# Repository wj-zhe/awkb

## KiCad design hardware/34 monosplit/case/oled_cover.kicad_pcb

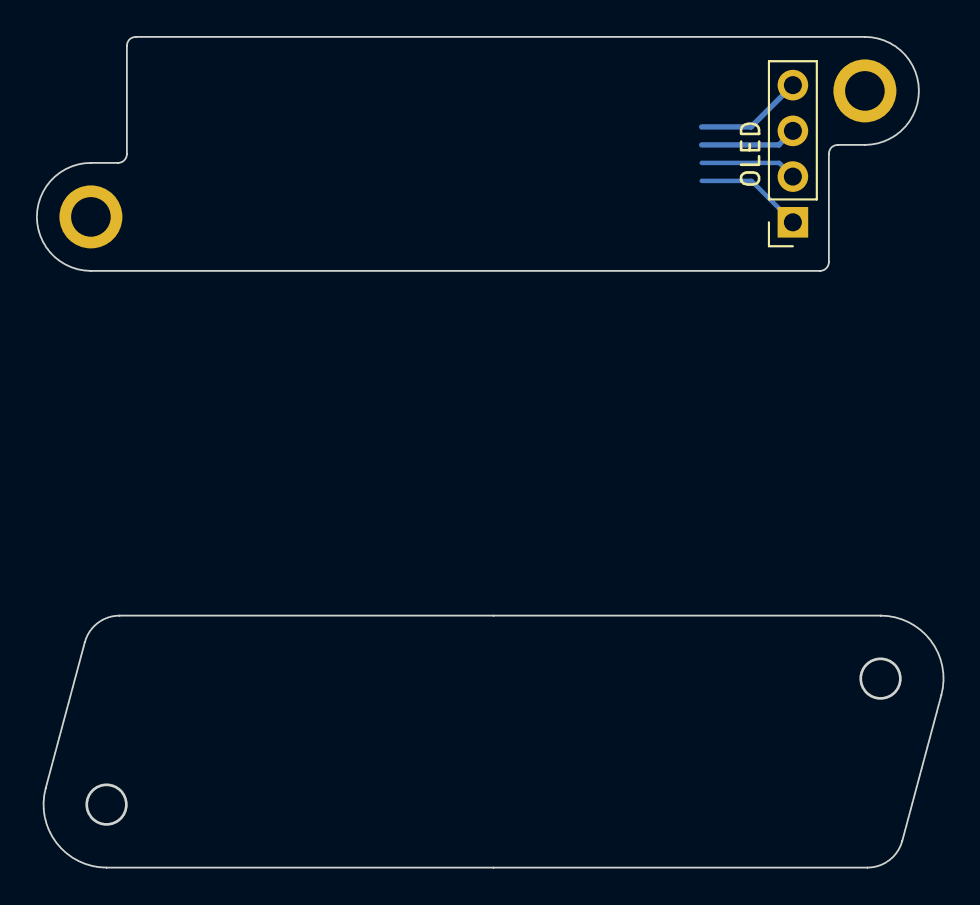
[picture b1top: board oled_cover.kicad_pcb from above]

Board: 2 copper layers, 49.0 x 13.0 mm, 6 parts (1 on the bottom side), 4 nets.

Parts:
J3: OLED; PinSocket_1x04_P2.54mm_Vertical
J4: Conn_01x04_Socket; Molex_200528-0040_1x04-1MP_P1.00mm_Horizontal
OH1, OH2: OLED cover; MountingHole_2.2mm_M2_ISO7380_Pad
OH3, OH4: OLED cover; MountingHole_2.2mm_M2_cutout

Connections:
GND_conn: J3.4, J4.4
SCL_conn: J3.2, J4.2
SDA_conn: J3.1, J4.1
VCC_conn: J3.3, J4.3

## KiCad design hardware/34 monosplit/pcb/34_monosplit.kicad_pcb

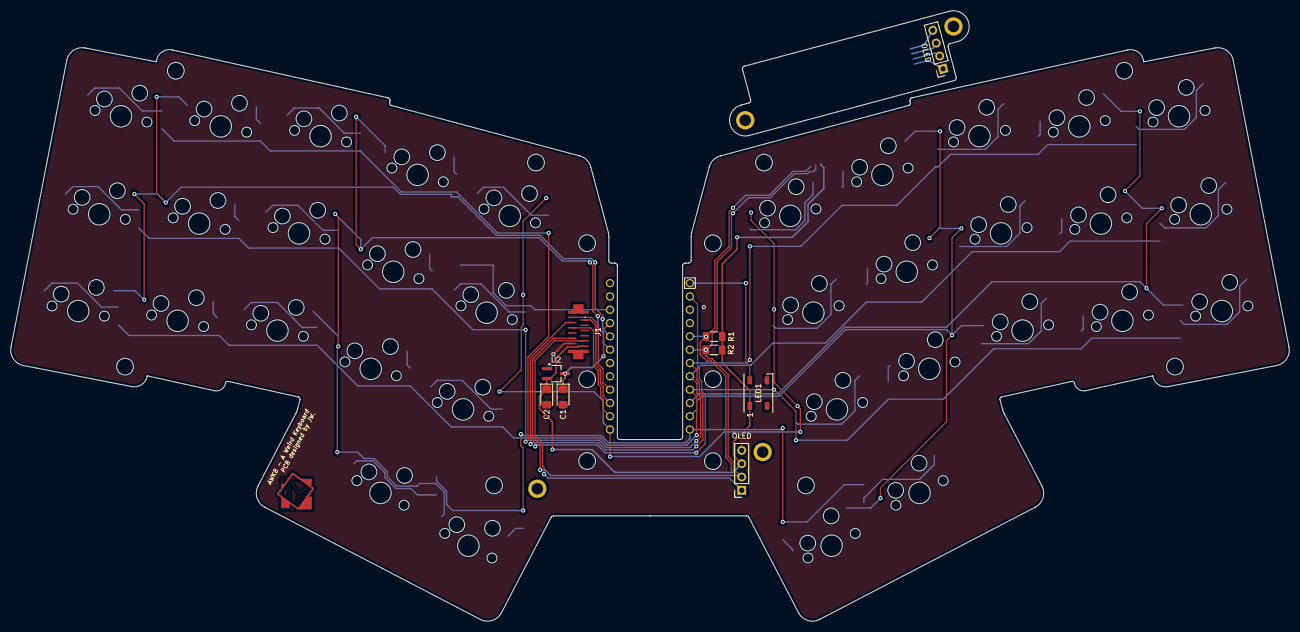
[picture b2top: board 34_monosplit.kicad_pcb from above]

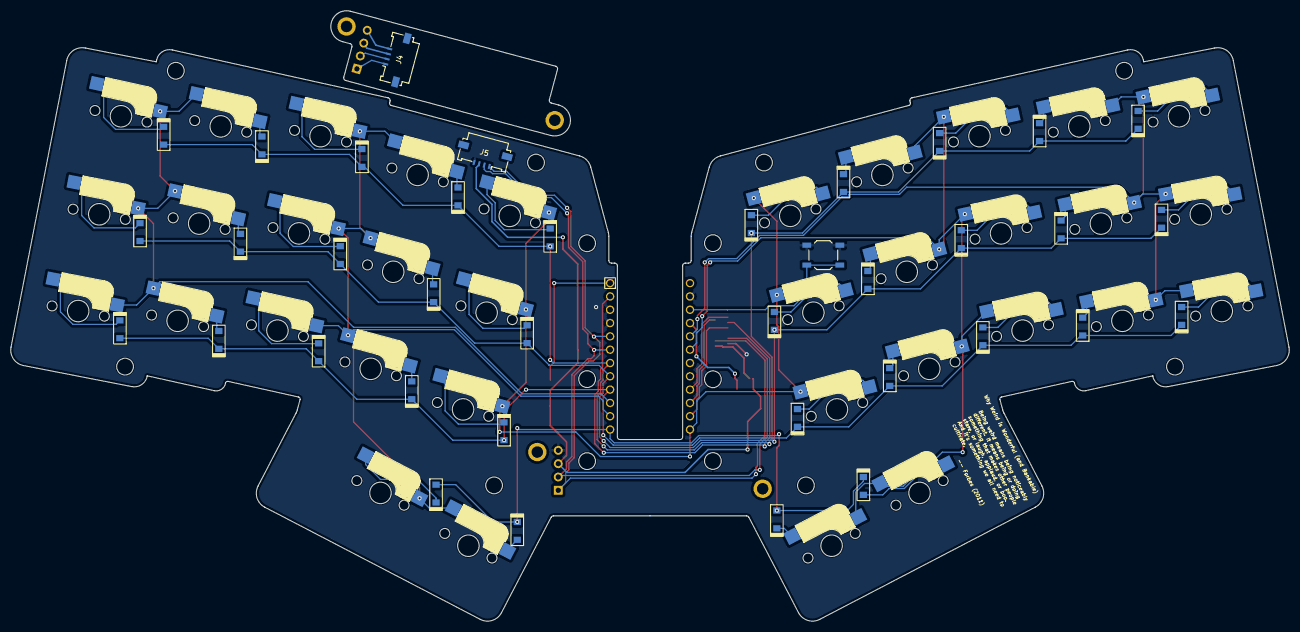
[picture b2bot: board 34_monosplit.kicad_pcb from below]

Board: 2 copper layers, 243.9 x 116.5 mm, 100 parts (38 on the bottom side), 58 nets.

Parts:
C1: 2.2uF; D_1206_3216Metric_Pad1.42x1.75mm_HandSolder
C2: 10uF; D_1206_3216Metric_Pad1.42x1.75mm_HandSolder
D1, D2, D3, D4, D5, D6, D7, D8, D9, D10, D11, D12, D13, D14, D15, D16, D17, D18, D19, D20, D21, D22, D23, D24, D25, D26, D27, D28, D29, D30, D31, D32, D33, D34: Diode; Diode_SOD123_SMD
H1: MountingHole_Pad; square_1
J1: Conn_01x12_Socket_vertical_no_lock; Hirose_FH12-12S-0.5SH_1x12-1MP_P0.50mm_Vertical_custom
J3, J6: OLED; PinSocket_1x04_P2.54mm_Vertical
J4, J5: Conn_01x04_Socket; Molex_200528-0040_1x04-1MP_P1.00mm_Horizontal
LED1: WS2812B; LED_WS2812B_PLCC4_5.0x5.0mm_P3.2mm
OH1, OH2, OH3, OH4: OLED cover; MountingHole_2.2mm_M2_ISO7380_Pad
R1, R2: 4.7k; R_1206_3216Metric_Pad1.30x1.75mm_HandSolder
Reset_Button1: SW_RST; SW_SPST_TL3342
SW1: SW1; CherryMX_Hotswap_single_side
SW2: SW2; CherryMX_Hotswap_single_side
SW3: SW3; CherryMX_Hotswap_single_side
SW4: SW4; CherryMX_Hotswap_single_side
SW5: SW5; CherryMX_Hotswap_single_side
SW6: SW6; CherryMX_Hotswap_single_side
SW7: SW7; CherryMX_Hotswap_single_side
SW8: SW8; CherryMX_Hotswap_single_side
SW9: SW9; CherryMX_Hotswap_single_side
SW10: SW10; CherryMX_Hotswap_single_side
SW11: SW11; CherryMX_Hotswap_single_side
SW12: SW12; CherryMX_Hotswap_single_side
SW13: SW13; CherryMX_Hotswap_single_side
SW14: SW14; CherryMX_Hotswap_single_side
SW15: SW15; CherryMX_Hotswap_single_side
SW16: SW16; CherryMX_Hotswap_single_side
SW17: SW17; CherryMX_Hotswap_single_side
SW18: SW18; CherryMX_Hotswap_single_side
SW19: SW19; CherryMX_Hotswap_single_side
SW20: SW20; CherryMX_Hotswap_single_side
SW21: SW21; CherryMX_Hotswap_single_side
SW22: SW22; CherryMX_Hotswap_single_side
SW23: SW23; CherryMX_Hotswap_single_side
SW24: SW24; CherryMX_Hotswap_single_side
SW25: SW25; CherryMX_Hotswap_single_side
SW26: SW26; CherryMX_Hotswap_single_side
SW27: SW27; CherryMX_Hotswap_single_side
SW28: SW28; CherryMX_Hotswap_single_side
SW29: SW29; CherryMX_Hotswap_single_side
SW30: SW30; CherryMX_Hotswap_single_side
SW31: SW31; CherryMX_Hotswap_single_side
SW32: SW32; CherryMX_Hotswap_single_side
SW33: SW33; CherryMX_Hotswap_single_side
SW34: SW34; CherryMX_Hotswap_single_side
TH1, TH2, TH3, TH4, TH5, TH6, TH7, TH8: Spacing plate; MountingHole_3.2mm_M3
TRH1, TRH2, TRH3, TRH4, TRH5, TRH6: Trackpad; MountingHole_3.2mm_M3
U1: ProMicro; ProMicro_1.1mm_hole_only
U2: XC6206P332MR; TSOT-23_HandSoldering

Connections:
GND: C1.2, C2.2, J1.2, J5.4, J6.4, LED1.3 (VSS), Reset_Button1.1, U1.3 (GND), U1.4 (GND), U1.23 (GND), U2.1 (GND)
GND_conn: J3.4, J4.4
LED: LED1.4 (DIN), U1.1 (TX(PD3))
MISO: J1.11, U1.15 (D14(PB3))
MOSI: J1.8, U1.14 (D16(PB2))
NCS: J1.10, U1.2 (RX(PD2))
unnamed: D1.2 (A), SW1.1
unnamed: D2.1 (K), SW2.2
unnamed: D3.2 (A), SW3.1
unnamed: D4.1 (K), SW4.2
unnamed: D5.2 (A), SW5.1
unnamed: D6.1 (K), SW6.2
unnamed: D7.2 (A), SW7.1
unnamed: D8.1 (K), SW8.2
unnamed: D9.2 (A), SW9.1
unnamed: D10.1 (K), SW10.2
unnamed: D11.2 (A), SW11.1
unnamed: D12.1 (K), SW12.2
unnamed: D13.2 (A), SW13.1
unnamed: D14.1 (K), SW14.2
unnamed: D15.2 (A), SW15.1
unnamed: D16.1 (K), SW16.2
unnamed: D17.2 (A), SW17.1
unnamed: D18.1 (K), SW18.2
unnamed: D19.2 (A), SW19.1
unnamed: D20.1 (K), SW20.2
unnamed: D21.2 (A), SW21.1
unnamed: D22.1 (K), SW22.2
unnamed: D23.2 (A), SW23.1
unnamed: D24.1 (K), SW24.2
unnamed: D25.2 (A), SW25.1
unnamed: D26.1 (K), SW26.2
unnamed: D27.2 (A), SW27.1
unnamed: D28.1 (K), SW28.2
unnamed: D29.2 (A), SW29.1
unnamed: D30.1 (K), SW30.2
unnamed: D31.2 (A), SW31.1
unnamed: D32.1 (K), SW32.2
unnamed: D33.2 (A), SW33.1
unnamed: D34.1 (K), SW34.2
RST: Reset_Button1.2, U1.22 (RST)
SCL: J1.4, J5.2, J6.2, R2.1, U1.6 (SCL(PD0))
SCLK: J1.12, U1.16 (D15(PB1))
SCL_conn: J3.2, J4.2
SDA: J1.3, J5.1, J6.1, R1.1, U1.5 (SDA(PD1))
SDA_conn: J3.1, J4.1
VCC: C1.1, U1.21 (VCC), U2.3 (VI)
VCC_3.3V: C2.1, J1.1, J5.3, J6.3, LED1.1 (VDD), R1.2, R2.2, U2.2 (VO)
VCC_conn: J3.3, J4.3
col0: SW1.2, SW2.1, SW11.2, SW12.1, SW21.2, SW22.1, U1.20 (A3(PF4))
col1: SW3.2, SW4.1, SW13.2, SW14.1, SW23.2, SW24.1, SW31.2, SW32.1, U1.19 (A2(PF5))
col2: SW5.2, SW6.1, SW15.2, SW16.1, SW25.2, SW26.1, U1.13 (D10(PB6))
col3: SW7.2, SW8.1, SW17.2, SW18.1, SW27.2, SW28.1, SW33.2, SW34.1, U1.11 (D8(PB4))
col4: SW9.2, SW10.1, SW19.2, SW20.1, SW29.2, SW30.1, U1.10 (D7(PE6))
row0: D1.1 (K), D2.2 (A), D3.1 (K), D4.2 (A), D5.1 (K), D6.2 (A), D7.1 (K), D8.2 (A), D9.1 (K), D10.2 (A), U1.7 (D4(PD4))
row1: D11.1 (K), D12.2 (A), D13.1 (K), D14.2 (A), D15.1 (K), D16.2 (A), D17.1 (K), D18.2 (A), D19.1 (K), D20.2 (A), U1.8 (D5(PC6))
row2: D21.1 (K), D22.2 (A), D23.1 (K), D24.2 (A), D25.1 (K), D26.2 (A), D27.1 (K), D28.2 (A), D29.1 (K), D30.2 (A), U1.9 (D6(PD7))
row3: D31.1 (K), D32.2 (A), D33.1 (K), D34.2 (A), U1.12 (D9(PB5))
